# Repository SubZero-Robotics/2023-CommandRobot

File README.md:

<div align="center">

<h3 align="center">2023 Command Robot</h3>

  <p align="center">
    Code for our 2023 robot. Built with the WPILib command-based framework.
    <br />
    <br />
    <a href="https://github.com/subzero-robotics/2023-commandRobot/issues">Current Issues</a>
    ·
    <a href="https://www.thebluealliance.com/team/5690/2023">The Blue Alliance</a>
  </p>
</div>

## Table of contents

- [Team 5690 SubZero Robotics 2023 Command Robot](#team-5690-subzero-robotics-2023-command-robot)
  - [Table of contents](#table-of-contents)
  - [About](#about)
  - [Development Cycle](#development-cycle)
    - [Main](#main)
    - [Competition](#competition)
  - [Subsystems](#subsystems)
  - [CAN IDs](#can-ids)
  - [Network Map](#network-map)
  - [Getting started](#getting-started)
    - [Prerequisites](#prerequisites)
  - [Making changes](#making-changes)
    - [Cloning the repo](#cloning-the-repo)
    - [Issues](#issues)
    - [Branches](#branches)
    - [Adding commits](#adding-commits)
    - [Pushing commits](#pushing-commits)
    - [Pulling branches](#pulling-branches)
    - [Pull requests](#pull-requests)
  - [Necessary Hardware](#necessary-hardware)
  - [Network Map](#network-map-1)
  - [Contact](#contact)

## About

:warning: **TODO: Add about section**

## Development Cycle

### Main

Main should **always** contain known, tested, and working code that has been throroughly verified by running it on the robot. Use other development branches to create new features and test them before pulling into `main` via a Pull Request (PR). `main` cannot have code pushed to it directly, meaning a PR is **mandatory**.

Use the `main` branch for non-competition usage and practice.

### Competition

Before a competition, create a new branch based on `main` and lock it via a GitHub protection rule to prevent pushes. Only use this branch during a competition to avoid unnecessary or breaking deployments to the RIO.

:warning: ***Changes should only be made to this branch if there is a blocking error that must be fixed immediately!*** :warning:

## Subsystems

Following the WPILib command based structure we have broken our robot up into a number of subsystems. They are listed below:

| Subsystem                                                             | Purpose                                                  |
| :-------------------------------------------------------------------- | :------------------------------------------------------- |
| [Brake](src/main/include/subsystems/BrakeSubsystem.h)                 | Set or unset brakes (supports brake mode and pneumatics) |
| [Drive](src/main/include/subsystems/DriveSubsystem.h)                 | Drives robot                                             |
| [Extension](src/main/include/subsystems/ExtensionSubsystem.h)         | Extends the arm                                          |
| [Intake](src/main/include/subsystems/IntakeSubsystem.h)               | Activates the intake                                     |
| [LEDController](src/main/include/subsystems/LEDControllerSubsystem.h) | Activates the LEDs (Does yellow and purple)              |
| [RotateArm](src/main/include/subsystems/RotateArmSubsystem.h)         | Rotates the arm                                          |
| [Wrist](src/main/include/subsystems/WristSubsystem.h)                 | Rotates the wrist                                        |

## CAN IDs

|     Purpose/Name     | CAN ID | Motor/Driver Type |
| :------------------: | :----: | :---------------: |
|   Left drive lead*    |   6    |      TalonFX      |
|  Left drive follow*   |   5    |      TalonFX      |
|   Right drive lead   |   8    |      TalonFX      |
|  Right drive follow  |   7    |      TalonFX      |
|  Lead arm rotation   |   1    |     SparkMax      |
| Follow arm rotation  |   3    |     SparkMax      |
|    Wrist rotation    |   15   |     SparkMax      |
|    Intake spinner    |   17   |     SparkMax      |
|   Extension motor*    |   50   |     SparkMax      |
| Pneumatic controller |   9    |       RevPH       |

\* = Inverted

## Network Map

|  Device   |             Address              |
| :-------: | :------------------------------: |
|  Gateway  | 10.56.90.1|
|  Gateway  | 10.56.90.129 (subject to change) |
|    RIO    |            10.56.90.2            |
|   Coral   |            10.56.90.4            |
| LimeLight |           10.56.90.11            |
|  Laptop   |             Dynamic              |

## Vision Service

The vision service is a systemd service that autostarts the python script on the Coral Dev Board on boot. 

### The vision.service File

The vision.service file contains the command to run the vision python script. The file is located at `/etc/systemd/system/vision.service`

### Restarting the Service

If you made a change to the vision.service file make sure to reload the daemon and the vision script with these commands:

1. `sudo systemctl daemon-reload`
2. `sudo systemctl restart vision`

### Checking Status

To check the status of the vision service, use this command:
`sudo systemctl status vision`

## Getting started

### Prerequisites

Install the following:

- [WPILib](https://docs.wpilib.org/en/stable/docs/getting-started/getting-started-frc-control-system/wpilib-setup.html)
- [Git](https://git-scm.com/download/win) (You don't need GitHub desktop)

## Making changes

### Cloning the repo

1. Install the [GitHub VS Code extension](vscode:extension/GitHub.vscode-pull-request-github)
2. Go to the GitHub tab and sign in using the account that has access to this repository
3. Click `Clone Repository` and search for `SubZero-Robotics/2023-CommandRobot`
4. Clone it into a known folder that has **no spaces** in its path
5. Open the repository in VS Code

### Issues

[GitHub issues](https://github.com/SubZero-Robotics/2023-CommandRobot/issues) are how we track which tasks need work along with who should be working on them. Pay attention to the issue number since this is how each one is uniquely identified. To create a new issue, visit the [issues tab in the repository](https://github.com/SubZero-Robotics/2023-CommandRobot/issues) and click `New issue`. Give it a descriptive title and enough information in the comment area so that anyone working on the issue knows exactly what needs to be changed/fixed. Additionally, assignees (who is working on it) and labels (what type of issue is this) can be assigned on the right.

### Branches

Branches are simply named pointers that point to a commit. Our main branch is called `main`, but we don't make changes to it directly. Instead, a new branch should be created before any code is modified. Click on the current branch in the bottom-left corner in VS Code and then click `+ Create new branch...`. The following naming conventions should be followed:

For a feature branch (major change):
`feature-<issue number>-<a few words describing the change>`

For a smaller, individual/small group branch:
`<first name>-<issue number>-<a few words describing the change>`

### Adding commits

After finishing a small change, such as modifying a method or adding a new file, a new commit should be made immediately. Go to the `Source Control` tab on the left side of VS Code and add the changed/added/deleted files from the `Changes` dropdown to `Staging` by clicking the `+`. Once the changes are staged, Type a **descriptive** commit message and then click the `Commit` button.

### Pushing commits

Commiting only applies the new commit locally. So to make it available to others in the repo, it needs to be pushed to the `remote` (GitHub's servers in this case). Either click `publish` in the `Source Control` tab if the branch hasn't been pushed before or `push` it otherwise to send the new commit to the remote's branch (this will be called `origin/<your branch's name>`).

### Pulling branches

If someone else has made their branch available on the remote, you might be wondering how other people can get those same commits into their local repo. This process is called `pulling`, and it involves downloading the remote's commits and merging them with the local branch's commits.

Sometimes, you might see a `merge conflict` appear which can happen if more than one person has worked on the same line in a file, thus making git unable to automatically merge them. To fix this, click on the conflicted file (denoted by a `!`) that opens the merge conflict editor. Once at the line(s) in question, either accept the incoming (one that exists on GitHub), the HEAD (the one that you have locally), or attempt to manually merge the two together by directly editing the line(s). Repeat this process for each line/file until all conflicts are resolved. Once done, stage the now-fixed files, create a new commit, and push.

### Pull requests

Now that all of your changes have been made (and *tested!*), it's time to get them merged into the main branch. Either click the `Create Pull Request` button in the `Source Control` tab (inline with the `SOURCE CONTROL` text, fourth one from the left) or go to the [`Pull requests` tab on GitHub](https://github.com/SubZero-Robotics/2023-CommandRobot/pulls), click `New pull request`, and set the `compare` branch to your branch. Fill in the template with a good title, a detailed description, a list of changes made, and the issue number before creating it. Assign a reviewer(s) on the right and label the PR accordingly.

The reviewer is responsible for looking over the PR, testing the changes themselves, and adding comments to the code changes if necessary. There are three possible actions a reviewer can take:

- Approve (PR is good; required to merge and should be done by a mentor or team lead)
- Disapprove (PR needs changes before it can be merged; please address the comments, click `Resolve` under each comment once fixed, then re-request a review)
- Comment (simply add a comment(s) without approving or disapproving)

## Necessary Hardware

1 Prototype 4 v2
2 Prototype 4

## Network Map

|  Device   |   Address   |
| :-------: | :---------: |
|  Gateway  | 10.56.90.1  |
|    RIO    | 10.56.90.2  |
|   Coral   | 10.56.90.4  |
| LimeLight | 10.56.90.11 |

## Contact

If you would like to contact the subzero robotics programmers, you can do so at [5690programmers@gmail.com](mailto:5690Programmers@gmail.com)

To contact the team directly, you can find us on [facebook](https://www.facebook.com/Esko-SubZero-Robotics-Team-5690-695407257248414/) or email us at [subzerorobotics@esko.k12.mn.us](mailto:subzerorobotics@esko.k12.mn.us)

Project Link: [https://github.com/subzero-robotics/2023-commandRobot](https://github.com/subzero-robotics/2023-commandRobot)

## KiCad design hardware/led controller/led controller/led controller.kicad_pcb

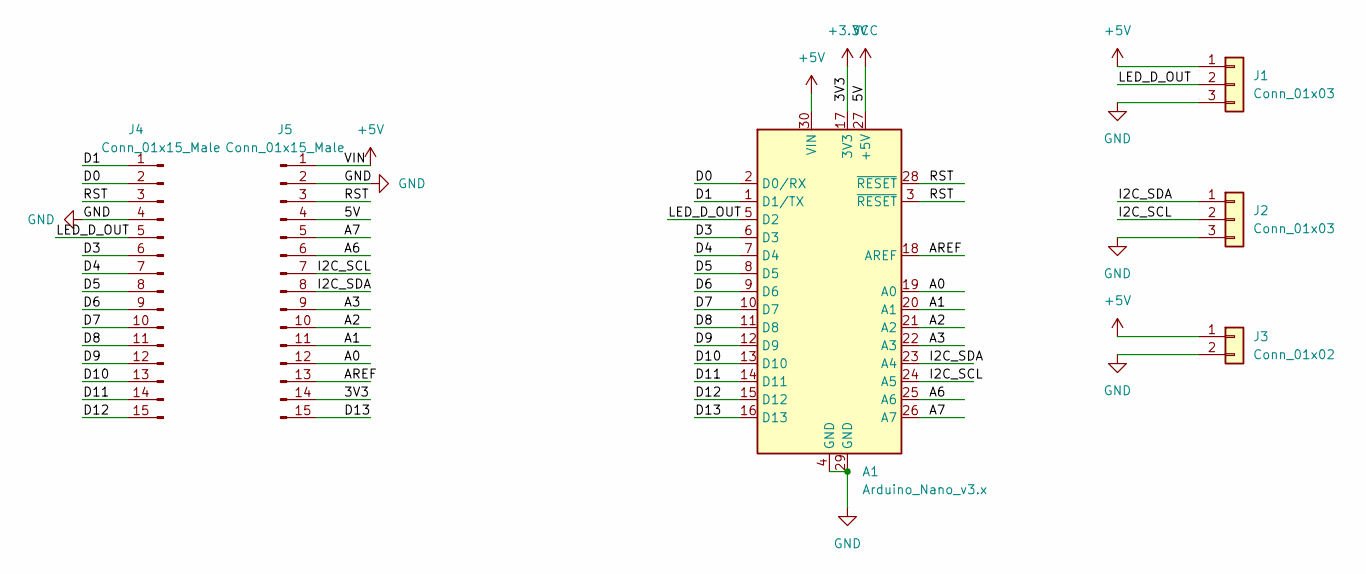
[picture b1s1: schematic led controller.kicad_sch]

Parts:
A1: Arduino_Nano_v3.x; Arduino_Nano
J1, J2: Conn_01x03; PinHeader_1x03_P2.54mm_Vertical
J3: Conn_01x02; PinHeader_1x02_P2.54mm_Vertical
J4, J5: Conn_01x15_Male

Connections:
+3.3V: A1.17 (3V3), J5.14
+5V: A1.30 (VIN), J1.1, J3.1, J5.1
/A0: A1.19 (A0), J5.12
/A1: A1.20 (A1), J5.11
/A2: A1.21 (A2), J5.10
/A3: A1.22 (A3), J5.9
/A6: A1.25 (A6), J5.6
/A7: A1.26 (A7), J5.5
/AREF: A1.18 (AREF), J5.13
/D0: A1.2 (D0/RX), J4.2
/D1: A1.1 (D1/TX), J4.1
/D3: A1.6 (D3), J4.6
/D4: A1.7 (D4), J4.7
/D5: A1.8 (D5), J4.8
/D6: A1.9 (D6), J4.9
/D7: A1.10 (D7), J4.10
/D8: A1.11 (D8), J4.11
/D9: A1.12 (D9), J4.12
/D10: A1.13 (D10), J4.13
/D11: A1.14 (D11), J4.14
/D12: A1.15 (D12), J4.15
/D13: A1.16 (D13), J5.15
/I2C_SCL: A1.24 (A5), J2.2, J5.7
/I2C_SDA: A1.23 (A4), J2.1, J5.8
/LED_D_OUT: A1.5 (D2), J1.2, J4.5
/RST: A1.3 (~RESET), A1.28 (~RESET), J4.3, J5.3
GND: A1.4 (GND), A1.29 (GND), J1.3, J2.3, J3.2, J4.4, J5.2
VCC: A1.27 (+5V), J5.4

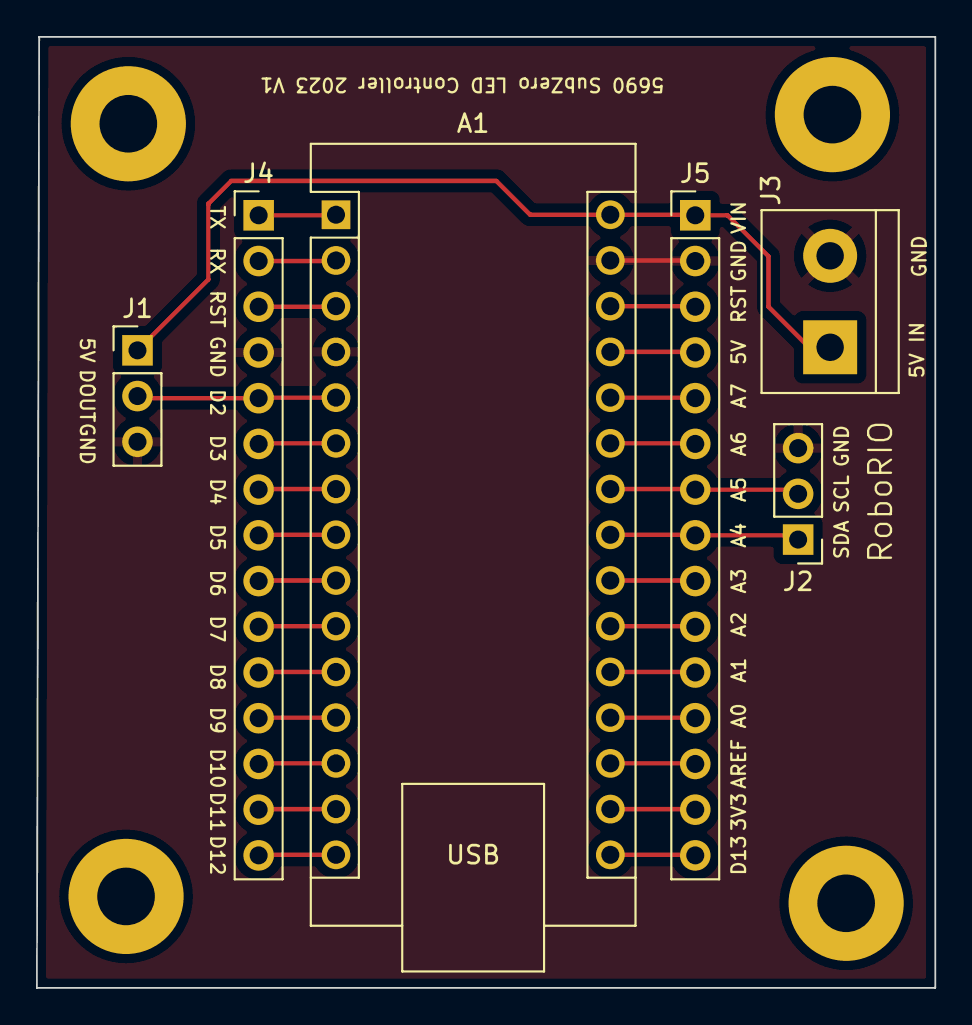
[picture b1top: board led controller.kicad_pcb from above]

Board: 2 copper layers, 49.9 x 52.8 mm, 10 parts (0 on the bottom side), 28 nets.

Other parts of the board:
H1, H2, H3, H4: MountingHole_3.2mm_M3_Pad

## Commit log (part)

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2023-02-06 created commands.h
2023-02-07 Add PatternRunner class
2023-02-08 Update PCB
2023-02-08 Create workflow for code formatting (#17)
    * Create workflow for code formatting
    * add .styleguide file
    * Create .clang-format
    * License for default style guide
    * change to different formatter workflow
    * test Google format
2023-02-08 Fix code style issues with clang_format
2023-02-08 Update PR template
2023-02-08 Python file linting
2023-02-08 install autopep8
2023-02-08 Fix code style issues with Autopep8
2023-02-09 Added patterns RGBFade, HackerMode, Chase, Wipe
2023-02-09 Initialize networktables.py and Add write method
2023-02-10 Finished Implementing patterns
2023-02-10 Add ReadPatternDone command
2023-02-10 network tables
2023-02-12 Added class parser
2023-02-12 Create dedicated package for utils
2023-02-13 RGB LED strip test menu
2023-02-13 Implement output flatten
2023-02-13 lots of lessons learned
2023-02-13 Create vision script
2023-02-14 Use cscore and ntcore
2023-02-15 Get vision script running
2023-02-15 Add CLI args
2023-02-15 Fix args
2023-02-15 Correct use of port
2023-02-15 Use of port
2023-02-15 Don't print newlines
2023-02-15 Jetson camera streaming script
2023-02-15 Update requirements
2023-02-16 Add ground plane to layer 2
2023-02-16 can ids for 2023 robot
2023-02-16 make it not bad
2023-02-17 Create static helper methods for DriveSubsystem
2023-02-17 limits on maxOutput
2023-02-17 make talon a reference
2023-02-17 use networktables 3
2023-02-17 remove underscores from private member talon
2023-02-17 create method for inverting a side
2023-02-18 fix build fail
2023-02-18 Differential drive using falcon500 (#22)
    * Initial differential drive implementation from 2022
    * Update DriveSubsystem.cpp
    Removed additional fluff from previous code
    * test on robot
    * Move changes from odometry branch to drive branch (#15)
    * change reference to subsystem
2023-02-18 Add Uno support
2023-02-18 create straightback functionalcommand
2023-02-18 Get LEDs to show
2023-02-18 Fixed RGBFade, Blink, SetColor, and HackerMode
2023-02-19 Fix reading color
2023-02-19 Start new pattern after setting
2023-02-20 Add frame saving script
2023-02-20 clarity
2023-02-20 Characterize drive, create test auto, start sim
2023-02-21 more sim "stuff"
2023-02-21 Add case
2023-02-21 RIO client
2023-02-22 fix errors
2023-02-22 errors
2023-02-22 RIO I2C Client (#23)
    * RIO client
    * Fix code style issues with clang_format
    * fix errors
    * Fix code style issues with clang_format
    * errors
    * Fix code style issues with clang_format
2023-02-22 Fix Networktables Integration
2023-02-23 scaffold effectorsubsystem
2023-02-23 RGB LED Controller (#21)
    * create arduino project
    * created led kicad board
    * base code for LED
    * Make code compile
    * defined commands
    * I2C buffer processing
2023-02-23 the rest of the auto
2023-02-23 Working Distance Based Auto (#25)
    * create straightback functionalcommand
    * create straightback functionalcommand
    * Characterize drive, create test auto, start sim
    * more sim "stuff"
    * the rest of the auto
    * Fix code style issues with clang_format
2023-02-23 skeleton remaining subsystems
2023-02-23 command to move arm
2023-02-23 Create VL53L1X RoboRIO Driver and Client
2023-02-24 Make active low
2023-02-25 scaffold extender
2023-02-25 Add new model
2023-02-25 fix NT
2023-02-25 Change dtype to uint8
2023-02-25 update stream
2023-02-25 Output camera stream to path
2023-02-25 Add stream
2023-02-25 get stream working
2023-02-25 Scale object detection output to frame size
2023-02-26 Update verbose output
2023-02-26 Create Jetson and Coral Vision Scripts (#19)
    * add pr template
    * Add Test Vision Script
    * Bounding box detection example (#16)
    * add pr template (#8)
    * Add example script for bounding boxes
    * Move to own folder
2023-02-26 start work on curved path
2023-02-26 Assigned bindings for everything but wrist
2023-02-26 Fix LED instantiation
2023-02-26 Modified extender to add limit switch
2023-02-26 more work on ramseteautobuilder
2023-02-26 finish pathplanner auto
2023-02-26 added TicksPerCm ad MaxArmDistance are constants
2023-02-26 add stupid outlineviewer file
2023-02-26 merge pathing to effector subsystem (#30)
    * start work on curved path
    * more work on ramseteautobuilder
    * finish pathplanner auto
    * add stupid outlineviewer file
    * Fix code style issues with clang_format
    ---------
2023-02-26 Created conceptual extension system, limit switch, and homing system
2023-02-26 intake subsystem
2023-02-26 Changed Name of MoveArm to RotateArm
2023-02-26 Whatever Nolan did
2023-02-26 Nolan 29 detection parser (#31)
    * Create Jetson and Coral Vision Scripts (#19)
    * add pr template
    * Add Test Vision Script
    * Bounding box detection example (#16)
    * add pr template (#8)
    * Add example script for bounding boxes
2023-02-26 fix merge conflict
2023-02-26 fix bugs
2023-02-27 Created base for rotation limit switches
2023-02-27 scaffold assist subsystem
2023-02-27 Correctly allocate vector memory
2023-02-27 detections Array parse from networktables
2023-02-27 Fixed misspelling
2023-02-27 Scaffold WristSubsystem
2023-02-27 Scaffold WristSubsystem (#32)
2023-02-27 Pathing (#33)
    * start work on curved path
    * more work on ramseteautobuilder
    * finish pathplanner auto
    * add stupid outlineviewer file
    * Fix code style issues with clang_format
    ---------
2023-02-27 sendablechooser for auto
2023-02-27 fix commandptr issue
2023-02-27 Fix command* issue
2023-02-28 logging of speeds
2023-02-28 Created base for Limelight system
2023-02-28 James limelight (#34)
    * Created base for Limelight system
    * Fix code style issues with clang_format
    ---------
2023-02-28 soft limit, name fixes
2023-02-28 Nano to old bootloader
2023-02-28 FIX BUGS MUAHAHAHA
2023-02-28 Camera Mount STL Files
    Prototype 4 is for the sides, Prototype 4 v2 is for the arm
2023-02-28 Camera Mount STL Files (#35)
    Prototype 4 is for the sides, Prototype 4 v2 is for the arm
2023-02-28 Update README.md (#37)
2023-02-28 soft limits
2023-03-01 Changed limit switches to digital
2023-03-01 Set to Coast mode on Initialization
2023-03-01 fixed build issues
2023-03-01 Created Brake mode
2023-03-01 Changed limit switches to digital (#38)
2023-03-01 Created Wrist homing abilities
2023-03-01 adjusted Wrist motor id
2023-03-01 get rid of compresser
2023-03-01 fixed gear ratio for arm
2023-03-01 Change to hall effect sensor
2023-03-01 fixes
2023-03-01 maek code werk
2023-03-01 oneshot commands
2023-03-01 Fixed Wrist and Wrist homing. Fixed button controls. Fixed LED displays. Added more constants.
2023-03-01 Added bounceback to limitswitches and added default state for intake
2023-03-02 last known working
2023-03-02 Last working before LSR
2023-03-02 fixed autos
2023-03-02 BRAKE MODE WORKING
2023-03-02 field day
2023-03-03 brake mode
2023-03-03 Chnaged LED system, created empty auto, changed reduced rotational modifier
2023-03-03 Fix extension logic
2023-03-04 update precision mode
2023-03-05 Fix extension logic (#50)
2023-03-05 Create single axis subsystem base class
2023-03-06 Fix autos
2023-03-06 check valid port
2023-03-06 update port check
2023-03-06 Add move semantics
2023-03-07 Use ProfiledPIDController
2023-03-07 ffmpeg frame capture
2023-03-07 Added to Subsystem readme and CAN ID readme
2023-03-07 Formated Document
2023-03-08 Move commands to header only
2023-03-08 readme
2023-03-08 default port
2023-03-08 Added to main.cpp for vl53l1x+
2023-03-08 Initialized SPI instance
2023-03-09 correct SPI behavior
2023-03-09 Default stream to root
2023-03-09 remove cache files
2023-03-09 Update Coral Stream (#51)
    * Default stream to root
    * remove cache files
    * Fix code style issues with Autopep8
    ---------
2023-03-09 update ip addresses
2023-03-09 Finished LIDAR subsystem
2023-03-10 remove depedency on absolute encoder
2023-03-11 Convert subsystems to base
2023-03-13 assist units
2023-03-13 logged AssistSubsystem Extender Rotation Wrist Positions and put them on smart dashboard
2023-03-14 fix logging
2023-03-14 More logging
2023-03-15 Tuned BaseSingleAxisSubsystem
2023-03-15 Kill Brakes
2023-03-15 Added logging for arm rotation, extension, and wrist subsystems.
2023-03-15 Remove units
2023-03-15 logging
2023-03-15 add model
2023-03-15 Arm WORKING
2023-03-15 fix bad
2023-03-16 lidar still broken :( (widePeepoSad)
2023-03-16 Update homing
2023-03-16 comment
2023-03-16 Do things the uncool way
2023-03-16 bindings
2023-03-16 update command usage
2023-03-16 use uint16_t
2023-03-16 use sparkmax pid
2023-03-16 Pathing update Nonworking
2023-03-16 Created PID Constants
2023-03-16 remove multi axis
2023-03-16 removed pids
2023-03-17 Start migration to position
2023-03-17 Use PID to set motor
2023-03-17 Remove unused command
2023-03-17 Don't use SPI
2023-03-17 multi axis arm
2023-03-17 pid dont werk
2023-03-18 revert joystick behavior
2023-03-18 don't overwrite if in deadzone
2023-03-18 anti gravity
2023-03-18 Fix scaling
2023-03-18 Create VL53L1X RoboRIO Driver and Client (#27)
    * Create VL53L1X RoboRIO Driver and Client
    * Fix code style issues with clang_format
    * Make active low
    * Fix code style issues with clang_format
    * Added to main.cpp for vl53l1x+
    * Fix code style issues with clang_format
2023-03-18 compiles
2023-03-18 c'est tres mal
2023-03-18 move antigravity
2023-03-18 correct override behavior
2023-03-18 fix autobuilder
2023-03-18 WORKING YASSSS
2023-03-18 more work on path following
2023-03-18 place and leave auto
2023-03-18 place and balance auto
2023-03-19 so many auto movements plus a surprise
2023-03-19 unnecessary this
2023-03-19 lidar mount
2023-03-19 Subsystem requirements lists
2023-03-19 pretty logging :^)
2023-03-20 lidar v2 mount
2023-03-20 update stdout logging
2023-03-20 Don't fall-through logging
2023-03-20 reference config
2023-03-20 update logging
2023-03-20 new model
2023-03-20 fix wrist gravity
2023-03-20 AutoPlaceHigh might work?
2023-03-21 wrist PID values and controller
2023-03-21 Fixed PIDs for rotate arm, extend arm, and rotate wrist
2023-03-21 Auto Place High, not fully working
2023-03-21 Remove colors :(
2023-03-21 Create robot picture
2023-03-21 Add uploaded photo to readme
2023-03-21 Change path for merge
    Photo won’t show until merged into main, refer to previous commit
2023-03-21 Add robot picture to readme (#56)
    * Create robot picture
    * Add uploaded photo to readme
    * Change path for merge
    Photo won’t show until merged into main, refer to previous commit
2023-03-21 fix commands
2023-03-21 lidar validation
2023-03-21 LEdeez
2023-03-21 more command stuff
2023-03-21 Adjust speeds
2023-03-21 wrist gravity
2023-03-21 Intake timer
2023-03-21 brake is back!!!
2023-03-21 funni
2023-03-21 Updated LIDAR
2023-03-22 All autos work
2023-03-22 might fix transient loopoverrun error with ledcontroller lockup
2023-03-22 closed as fixed
2023-03-22 sendable chooser
2023-03-23 refactor auto placement
2023-03-23 Refactor subsystems, add auto intake
2023-03-23 New branch for iowa testing, removed outtake after auto place high
2023-03-23 fix placeandbalance auto
2023-03-23 readd pneumatic brakes
2023-03-23 just commiting to save changes real quick
2023-03-23 started on fixing brake mode
2023-03-23 Added LEDs to Brake Mode
2023-03-24 Might work?
2023-03-24 properly set brake modes
2023-03-24 set brakes on disable
2023-03-25 vision updates
2023-03-25 rename arg
2023-03-25 update help
2023-03-25 Fix Juicy Cubes and Update Readme
2023-04-03 revert to before the CSA touched it
2023-04-13 Improve Documentation, New Constants, Logging Min Level
2023-04-14 consolidate axis multipliers
2023-04-14 Arm Subsystems, Autos, and Refactor (#53)
2023-04-14 Pathplanner Changes
2023-04-19 transmit delay over I2C
